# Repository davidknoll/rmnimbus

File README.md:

Projects and tools I've made while tinkering with the RM Nimbus PC-186 & PC-386
===============================================================================

Unless otherwise stated, anything here that was made by me can be used/distributed/etc under the MIT license, and none of it is approved or endorsed by [RM plc](https://www.rm.com/).

* ***8087repro*** - Reproduction of the 8087 option board for the PC-186, using a DS1100 delay line IC instead of EP8274. Prototype PCB passes basic testing.
* ***idecf*** - Ideas for how to attach a CF card to the PC-386, which uses the MCA bus so the right hardware can be harder to find.
* ***joysticksplitter*** - Allows two Atari/Commodore joysticks to be connected, as mentioned in sections 2.5.5 and 2.16.4 of the Service Manual. Two buttons are supported per joystick on pins 6 and 9, with power on pin 7. Not yet built/tested.
* ***nimbuscd*** - This contains some experiments with using a SCSI CD-ROM drive (initially, emulated with BlueSCSI) on the PC-186 with original DCB. I'm hoping to make it into `nimbuscd.sys`, a CD-ROM device driver to use with MSCDEX.
* ***nimbusmouse*** - I saw [this PS/2 mouse adaptor](https://www.thenimbus.co.uk/upgrades-and-maintenance/ps2mouse) and thought it could be done with a smaller microcontroller (specifically, an ATtiny2313 using [ATTinyCore](https://github.com/SpenceKonde/ATTinyCore)).
  * My version isn't working at the moment, but I've had aspects of it working. Work in progress.
* ***nimbusrtc*** - Attach a DS12C887A RTC pretty much directly to the bus as an expansion card.
  * This and similar RTCs are made for a multiplexed bus, so no extra latches and buffers are necessary. But because the Nimbus I/O bus is just half of a 16-bit bus, it only sees accesses where A0 is 0. The bus is shifted by one bit to make sure A0 can be 0 and the RTC registers can all still be accessed. The shift is reversed in software.
  * Not all of the RTC's RAM is accessible due to the available address space in one slot. Only chip selects 0, 2 and 4 can be used, as we also need to make sure A7 is 0 to address the right half of the RTC. Chip select 0 and interrupt 0 are generally reserved for the disk controller. An interrupt is unnecessary for the RTC if only using simple get/set commands.
  * There is a device driver that can be loaded from CONFIG.SYS to use the RTC on startup and with the TIME and DATE commands.
  * Alternatively, the get/set commands provided can be compiled on the Nimbus itself using Microsoft QuickC under SETPC. They default to expecting the RTC in slot 4, but this can be set with a switch ```/0``` - ```/4```.
* ***PC-386 RAM*** - Incomplete attempts at reproducing a decent size memory module for the PC-386.
* ***Piconet transceiver*** - Facilitates connecting a microcontroller to Piconet. Prototype PCBs so far untested- suspected pinout problem.
* ***piexpansion*** - Put a Raspberry Pi Pico W with an SD card on the PC-186 expansion bus, to hopefully emulate any physical expansion card, even the disk controller. Prototype PCB passes basic testing.
* ***reink*** - Generate block 0 for SCSI disks of any geometry, so you're not restricted to the few models in HDFORM.
  * This doesn't write the sector to the disk itself, as I don't have access to the system programmer's manual that would probably tell me how to do that. The sector is written to stdout instead, and you'll need to write it to the disk separately. (Which is made a whole lot simpler if using a SCSI2SD.)
  * You then need to run STAMP and/or HARDDISK on the Nimbus to partition the disk. I found a 64MB limit on DOS partition size, with only one DOS partition supported per disk.
  * This is not a replacement for an actual low-level format if you need one.
* ***simmadaptor*** - Adaptors for 30 or 72 pin SIMMs on the 186. Not yet tested, prototype PCBs ordered.
* ***ymplay*** - Play YM chiptune audio files using the AY-3-8910 in the Nimbus.

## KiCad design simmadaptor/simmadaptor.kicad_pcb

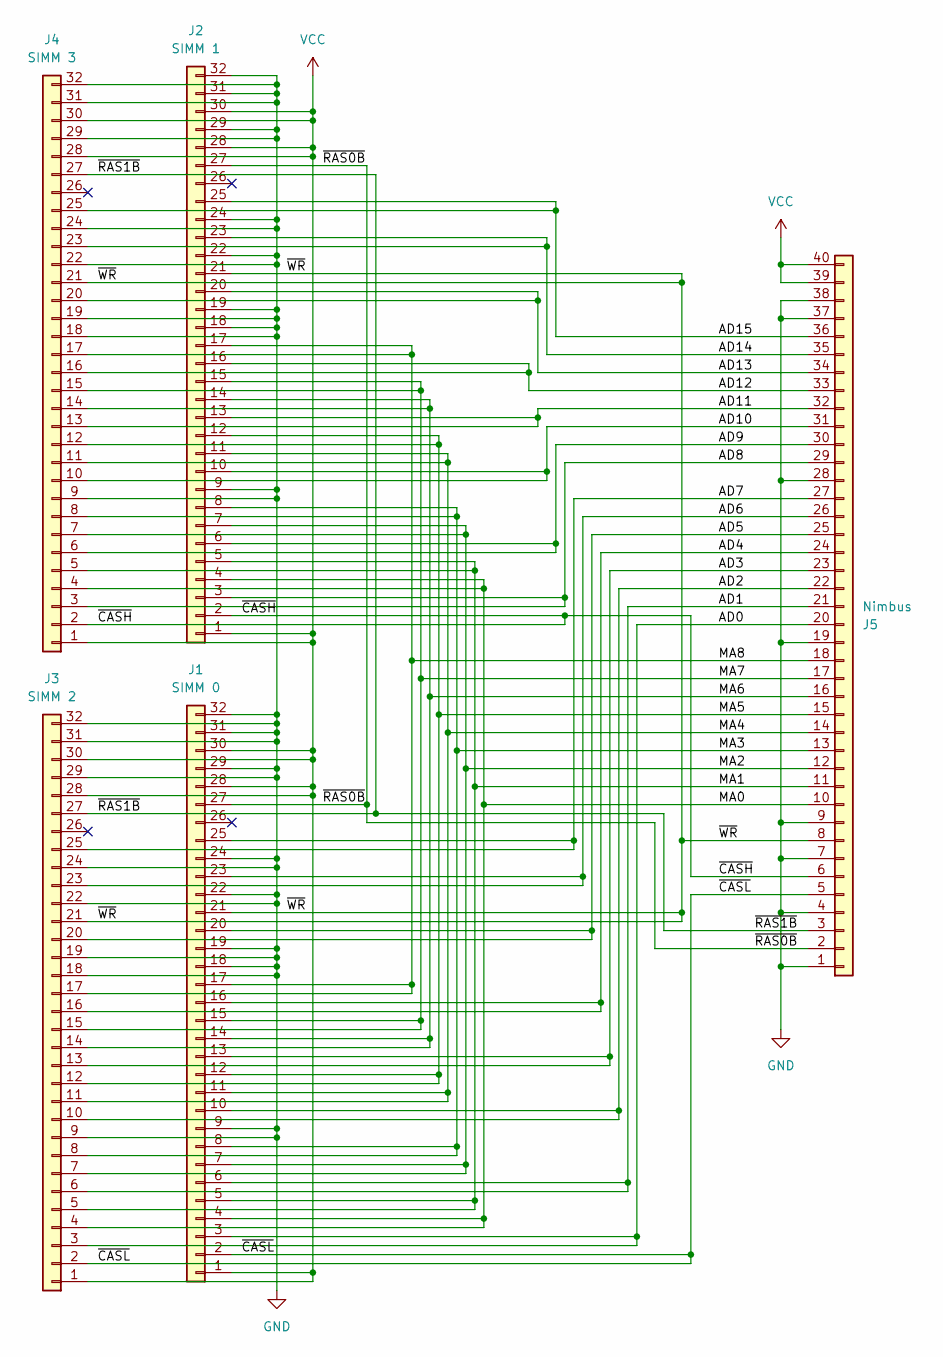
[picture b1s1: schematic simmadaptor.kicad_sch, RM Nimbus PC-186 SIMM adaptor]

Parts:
J1: SIMM 0; SIMM
J2: SIMM 1; SIMM
J3: SIMM 2; SIMM
J4: SIMM 3; SIMM
J5: Nimbus; PinSocket_1x40_P2.54mm_Horizontal

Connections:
/AD0: J1.3, J3.3, J5.20
/AD1: J1.6, J3.6, J5.21
/AD2: J1.10, J3.10, J5.22
/AD3: J1.13, J3.13, J5.23
/AD4: J1.16, J3.16, J5.24
/AD5: J1.20, J3.20, J5.25
/AD6: J1.23, J3.23, J5.26
/AD7: J1.25, J3.25, J5.27
/AD8: J2.3, J4.3, J5.29
/AD9: J2.6, J4.6, J5.30
/AD10: J2.10, J4.10, J5.31
/AD11: J2.13, J4.13, J5.32
/AD12: J2.16, J4.16, J5.33
/AD13: J2.20, J4.20, J5.34
/AD14: J2.23, J4.23, J5.35
/AD15: J2.25, J4.25, J5.36
/MA0: J1.4, J2.4, J3.4, J4.4, J5.10
/MA1: J1.5, J2.5, J3.5, J4.5, J5.11
/MA2: J1.7, J2.7, J3.7, J4.7, J5.12
/MA3: J1.8, J2.8, J3.8, J4.8, J5.13
/MA4: J1.11, J2.11, J3.11, J4.11, J5.14
/MA5: J1.12, J2.12, J3.12, J4.12, J5.15
/MA6: J1.14, J2.14, J3.14, J4.14, J5.16
/MA7: J1.15, J2.15, J3.15, J4.15, J5.17
/MA8: J1.17, J2.17, J3.17, J4.17, J5.18
/~CASH: J2.2, J4.2, J5.6
/~CASL: J1.2, J3.2, J5.5
/~RAS0B: J1.27, J2.27, J5.2
/~RAS1B: J3.27, J4.27, J5.3
/~WR: J1.21, J2.21, J3.21, J4.21, J5.8
GND: J1.9, J1.18, J1.19, J1.22, J1.24, J1.29, J1.31, J1.32, J2.9, J2.18, J2.19, J2.22, J2.24, J2.29, J2.31, J2.32, J3.9, J3.18, J3.19, J3.22, J3.24, J3.29, J3.31, J3.32, J4.9, J4.18, J4.19, J4.22, J4.24, J4.29, J4.31, J4.32, J5.1, J5.4, J5.7, J5.9, J5.19, J5.28, J5.37, J5.38
VCC: J1.1, J1.28, J1.30, J2.1, J2.28, J2.30, J3.1, J3.28, J3.30, J4.1, J4.28, J4.30, J5.39, J5.40

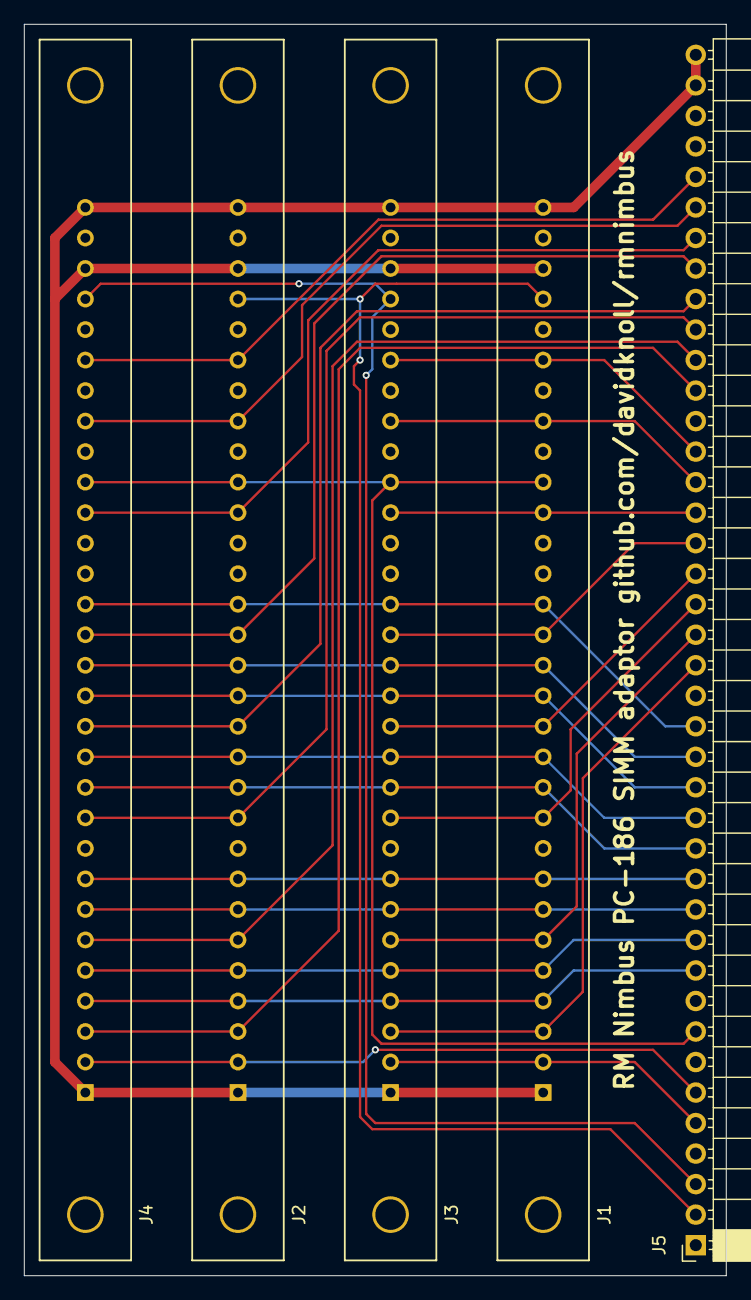
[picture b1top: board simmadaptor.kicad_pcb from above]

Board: 2 copper layers, 58.4 x 104.1 mm, 5 parts (0 on the bottom side), 32 nets.

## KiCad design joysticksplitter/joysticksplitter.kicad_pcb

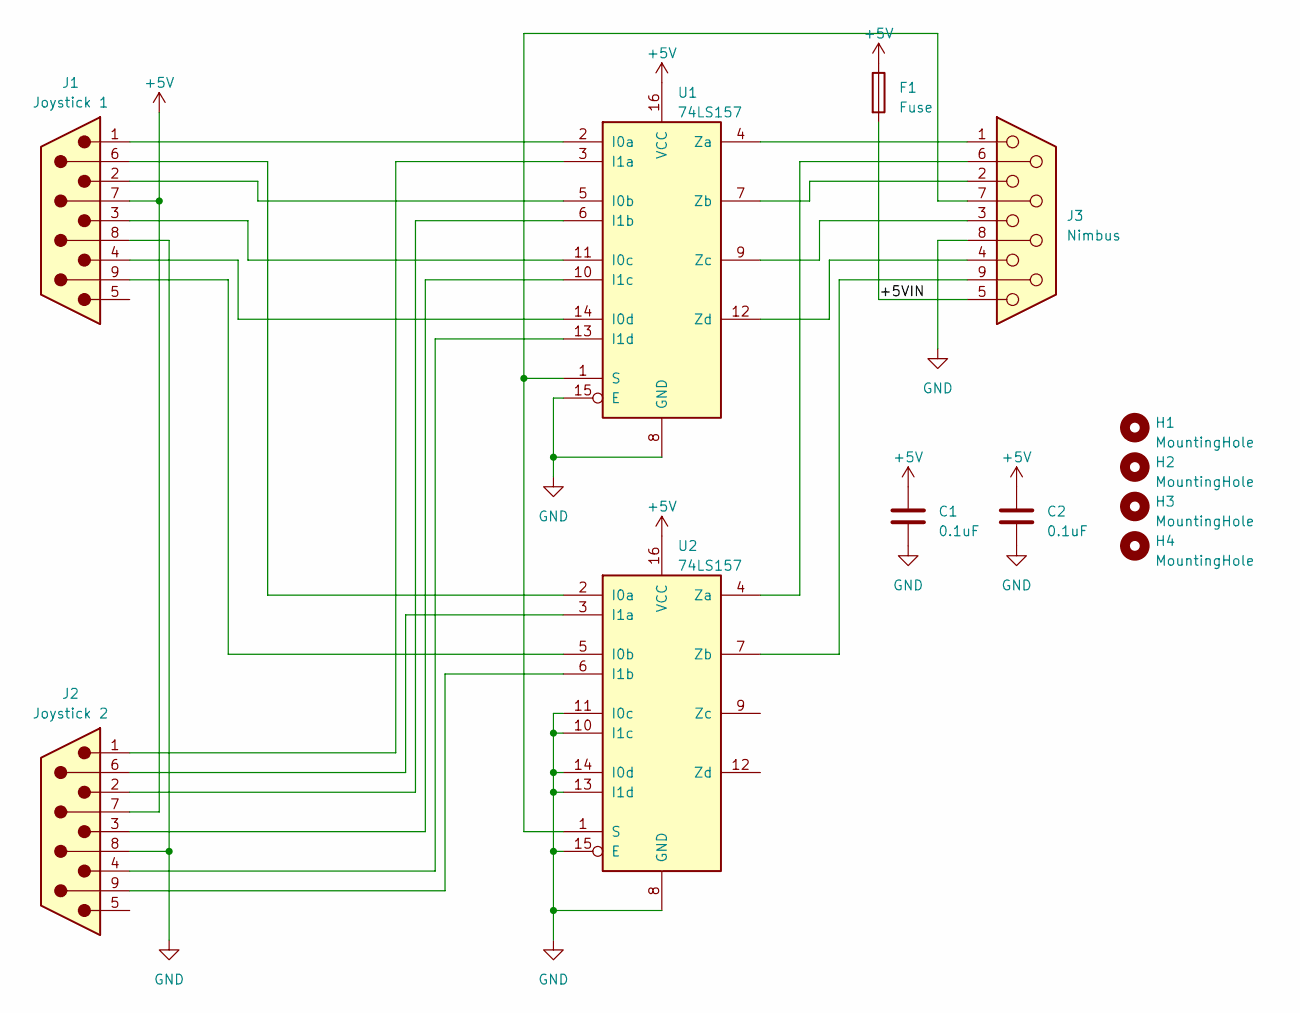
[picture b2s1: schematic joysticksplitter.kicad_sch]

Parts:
C1, C2: 0.1uF; C_Disc_D4.3mm_W1.9mm_P5.00mm
F1: Fuse; Fuse_Littelfuse_395Series
H1, H2, H3, H4: MountingHole; MountingHole_3.2mm_M3
J1: Joystick 1; DSUB-9_Male_EdgeMount_P2.77mm
J2: Joystick 2; DSUB-9_Male_EdgeMount_P2.77mm
J3: Nimbus; DSUB-9_Female_Horizontal_P2.77x2.84mm_EdgePinOffset9.40mm
U1, U2: 74LS157; DIP-16_W7.62mm_Socket

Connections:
+5V: C1.1, C2.1, F1.1, J1.7, J2.7, U1.16 (VCC), U2.16 (VCC)
/+5VIN: F1.2, J3.5
GND: C1.2, C2.2, J1.8, J2.8, J3.8, U1.8 (GND), U1.15 (E), U2.8 (GND), U2.10 (I1c), U2.11 (I0c), U2.13 (I1d), U2.14 (I0d), U2.15 (E)
unnamed: J1.1, U1.2 (I0a)
unnamed: J1.2, U1.5 (I0b)
unnamed: J1.3, U1.11 (I0c)
unnamed: J1.4, U1.14 (I0d)
unnamed: J2.1, U1.3 (I1a)
unnamed: J2.2, U1.6 (I1b)
unnamed: J2.3, U1.10 (I1c)
unnamed: J2.4, U1.13 (I1d)
unnamed: J3.7, U1.1 (S), U2.1 (S)
unnamed: J3.1, U1.4 (Za)
unnamed: J3.2, U1.7 (Zb)
unnamed: J3.3, U1.9 (Zc)
unnamed: J3.4, U1.12 (Zd)
unnamed: J1.6, U2.2 (I0a)
unnamed: J1.9, U2.5 (I0b)
unnamed: J2.6, U2.3 (I1a)
unnamed: J2.9, U2.6 (I1b)
unnamed: J3.6, U2.4 (Za)
unnamed: J3.9, U2.7 (Zb)

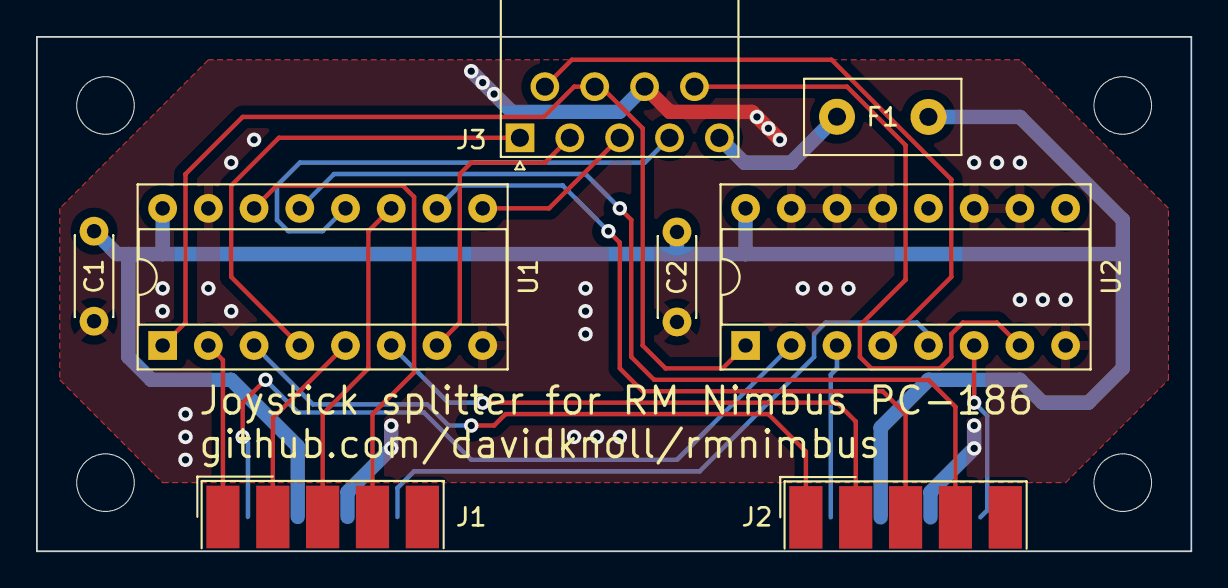
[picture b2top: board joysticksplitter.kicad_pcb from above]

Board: 2 copper layers, 64.1 x 28.6 mm, 12 parts (0 on the bottom side), 22 nets.

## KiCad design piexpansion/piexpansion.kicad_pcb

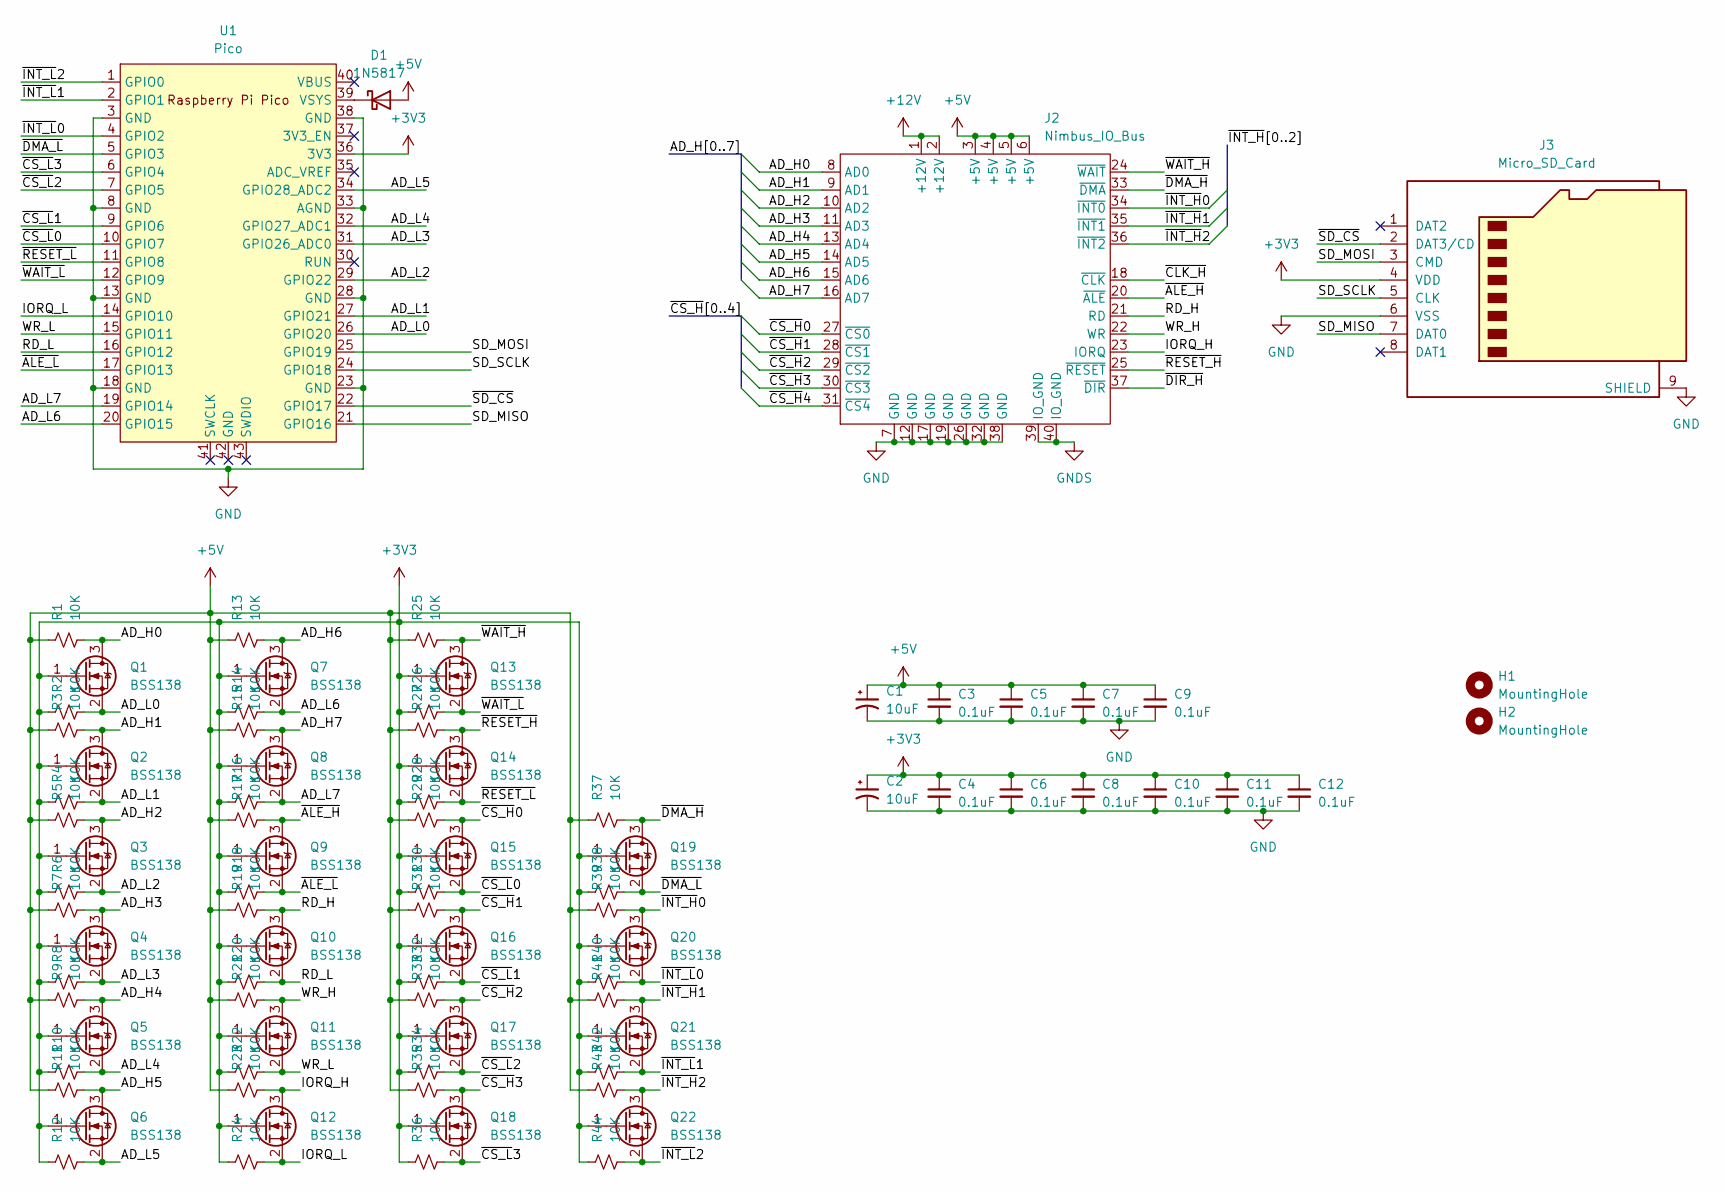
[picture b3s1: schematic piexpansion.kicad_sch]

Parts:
C1, C2: 10uF; CP_Radial_D6.3mm_P2.50mm
C3, C4, C5, C6, C7, C8, C9, C10, C11, C12: 0.1uF; C_0805_2012Metric_Pad1.18x1.45mm_HandSolder
D1: 1N5817; D_DO-41_SOD81_P10.16mm_Horizontal
H1, H2: MountingHole; MountingHole_4mm
J2: Nimbus_IO_Bus; IDC-Header_2x20-1MP_P2.54mm_Latch_Horizontal
J3: Micro_SD_Card; microSD_HC_Wuerth_693072010801
Q1, Q2, Q3, Q4, Q5, Q6, Q7, Q8, Q9, Q10, Q11, Q12, Q13, Q14, Q15, Q16, Q17, Q18, Q19, Q20, Q21, Q22: BSS138; SOT-23
R1, R2, R3, R4, R5, R6, R7, R8, R9, R10, R11, R12, R13, R14, R15, R16, R17, R18, R19, R20, R21, R22, R23, R24, R25, R26, R27, R28, R29, R30, R31, R32, R33, R34, R35, R36, R37, R38, R39, R40, R41, R42, R43, R44: 10K; R_0805_2012Metric_Pad1.20x1.40mm_HandSolder
U1: Pico; RPi_Pico_SMD_TH

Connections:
+3V3: C2.1, C4.1, C6.1, C8.1, C10.1, C11.1, C12.1, J3.4 (VDD), Q1.1 (G), Q2.1 (G), Q3.1 (G), Q4.1 (G), Q5.1 (G), Q6.1 (G), Q7.1 (G), Q8.1 (G), Q9.1 (G), Q10.1 (G), Q11.1 (G), Q12.1 (G), Q13.1 (G), Q14.1 (G), Q15.1 (G), Q16.1 (G), Q17.1 (G), Q18.1 (G), Q19.1 (G), Q20.1 (G), Q21.1 (G), Q22.1 (G), R2.1, R4.1, R6.1, R8.1, R10.1, R12.1, R14.1, R16.1, R18.1, R20.1, R22.1, R24.1, R26.1, R28.1, R30.1, R32.1, R34.1, R36.1, R38.1, R40.1, R42.1, R44.1, U1.36 (3V3)
+5V: C1.1, C3.1, C5.1, C7.1, C9.1, D1.2 (A), J2.3 (+5V), J2.4 (+5V), J2.5 (+5V), J2.6 (+5V), R1.1, R3.1, R5.1, R7.1, R9.1, R11.1, R13.1, R15.1, R17.1, R19.1, R21.1, R23.1, R25.1, R27.1, R29.1, R31.1, R33.1, R35.1, R37.1, R39.1, R41.1, R43.1
+12V: J2.1 (+12V), J2.2 (+12V)
/AD_H0: J2.8 (AD0), Q1.3 (D), R1.2
/AD_H1: J2.9 (AD1), Q2.3 (D), R3.2
/AD_H2: J2.10 (AD2), Q3.3 (D), R5.2
/AD_H3: J2.11 (AD3), Q4.3 (D), R7.2
/AD_H4: J2.13 (AD4), Q5.3 (D), R9.2
/AD_H5: J2.14 (AD5), Q6.3 (D), R11.2
/AD_H6: J2.15 (AD6), Q7.3 (D), R13.2
/AD_H7: J2.16 (AD7), Q8.3 (D), R15.2
/AD_L0: Q1.2 (S), R2.2, U1.26 (GPIO20)
/AD_L1: Q2.2 (S), R4.2, U1.27 (GPIO21)
/AD_L2: Q3.2 (S), R6.2, U1.29 (GPIO22)
/AD_L3: Q4.2 (S), R8.2, U1.31 (GPIO26_ADC0)
/AD_L4: Q5.2 (S), R10.2, U1.32 (GPIO27_ADC1)
/AD_L5: Q6.2 (S), R12.2, U1.34 (GPIO28_ADC2)
/AD_L6: Q7.2 (S), R14.2, U1.20 (GPIO15)
/AD_L7: Q8.2 (S), R16.2, U1.19 (GPIO14)
/IORQ_H: J2.23 (IORQ), Q12.3 (D), R23.2
/IORQ_L: Q12.2 (S), R24.2, U1.14 (GPIO10)
/RD_H: J2.21 (RD), Q10.3 (D), R19.2
/RD_L: Q10.2 (S), R20.2, U1.16 (GPIO12)
/SD_MISO: J3.7 (DAT0), U1.21 (GPIO16)
/SD_MOSI: J3.3 (CMD), U1.25 (GPIO19)
/SD_SCLK: J3.5 (CLK), U1.24 (GPIO18)
/WR_H: J2.22 (WR), Q11.3 (D), R21.2
/WR_L: Q11.2 (S), R22.2, U1.15 (GPIO11)
/~ALE_H: J2.20 (~ALE), Q9.3 (D), R17.2
/~ALE_L: Q9.2 (S), R18.2, U1.17 (GPIO13)
/~CLK_H: J2.18 (~CLK)
/~CS_H0: J2.27 (~CS0), Q15.3 (D), R29.2
/~CS_H1: J2.28 (~CS1), Q16.3 (D), R31.2
/~CS_H2: J2.29 (~CS2), Q17.3 (D), R33.2
/~CS_H3: J2.30 (~CS3), Q18.3 (D), R35.2
/~CS_H4: J2.31 (~CS4)
/~CS_L0: Q15.2 (S), R30.2, U1.10 (GPIO7)
/~CS_L1: Q16.2 (S), R32.2, U1.9 (GPIO6)
/~CS_L2: Q17.2 (S), R34.2, U1.7 (GPIO5)
/~CS_L3: Q18.2 (S), R36.2, U1.6 (GPIO4)
/~DIR_H: J2.37 (~DIR)
/~DMA_H: J2.33 (~DMA), Q19.3 (D), R37.2
/~DMA_L: Q19.2 (S), R38.2, U1.5 (GPIO3)
/~INT_H0: J2.34 (~INT0), Q20.3 (D), R39.2
/~INT_H1: J2.35 (~INT1), Q21.3 (D), R41.2
/~INT_H2: J2.36 (~INT2), Q22.3 (D), R43.2
/~INT_L0: Q20.2 (S), R40.2, U1.4 (GPIO2)
/~INT_L1: Q21.2 (S), R42.2, U1.2 (GPIO1)
/~INT_L2: Q22.2 (S), R44.2, U1.1 (GPIO0)
/~RESET_H: J2.25 (~RESET), Q14.3 (D), R27.2
/~RESET_L: Q14.2 (S), R28.2, U1.11 (GPIO8)
/~SD_CS: J3.2 (DAT3/CD), U1.22 (GPIO17)
/~WAIT_H: J2.24 (~WAIT), Q13.3 (D), R25.2
/~WAIT_L: Q13.2 (S), R26.2, U1.12 (GPIO9)
GND: C1.2, C2.2, C3.2, C4.2, C5.2, C6.2, C7.2, C8.2, C9.2, C10.2, C11.2, C12.2, J2.7 (GND), J2.12 (GND), J2.17 (GND), J2.19 (GND), J2.26 (GND), J2.32 (GND), J2.38 (GND), J3.6 (VSS), J3.9 (SHIELD), U1.3 (GND), U1.8 (GND), U1.13 (GND), U1.18 (GND), U1.23 (GND), U1.28 (GND), U1.33 (AGND), U1.38 (GND)
GNDS: J2.39 (IO_GND), J2.40 (IO_GND)
unnamed: D1.1 (K), U1.39 (VSYS)

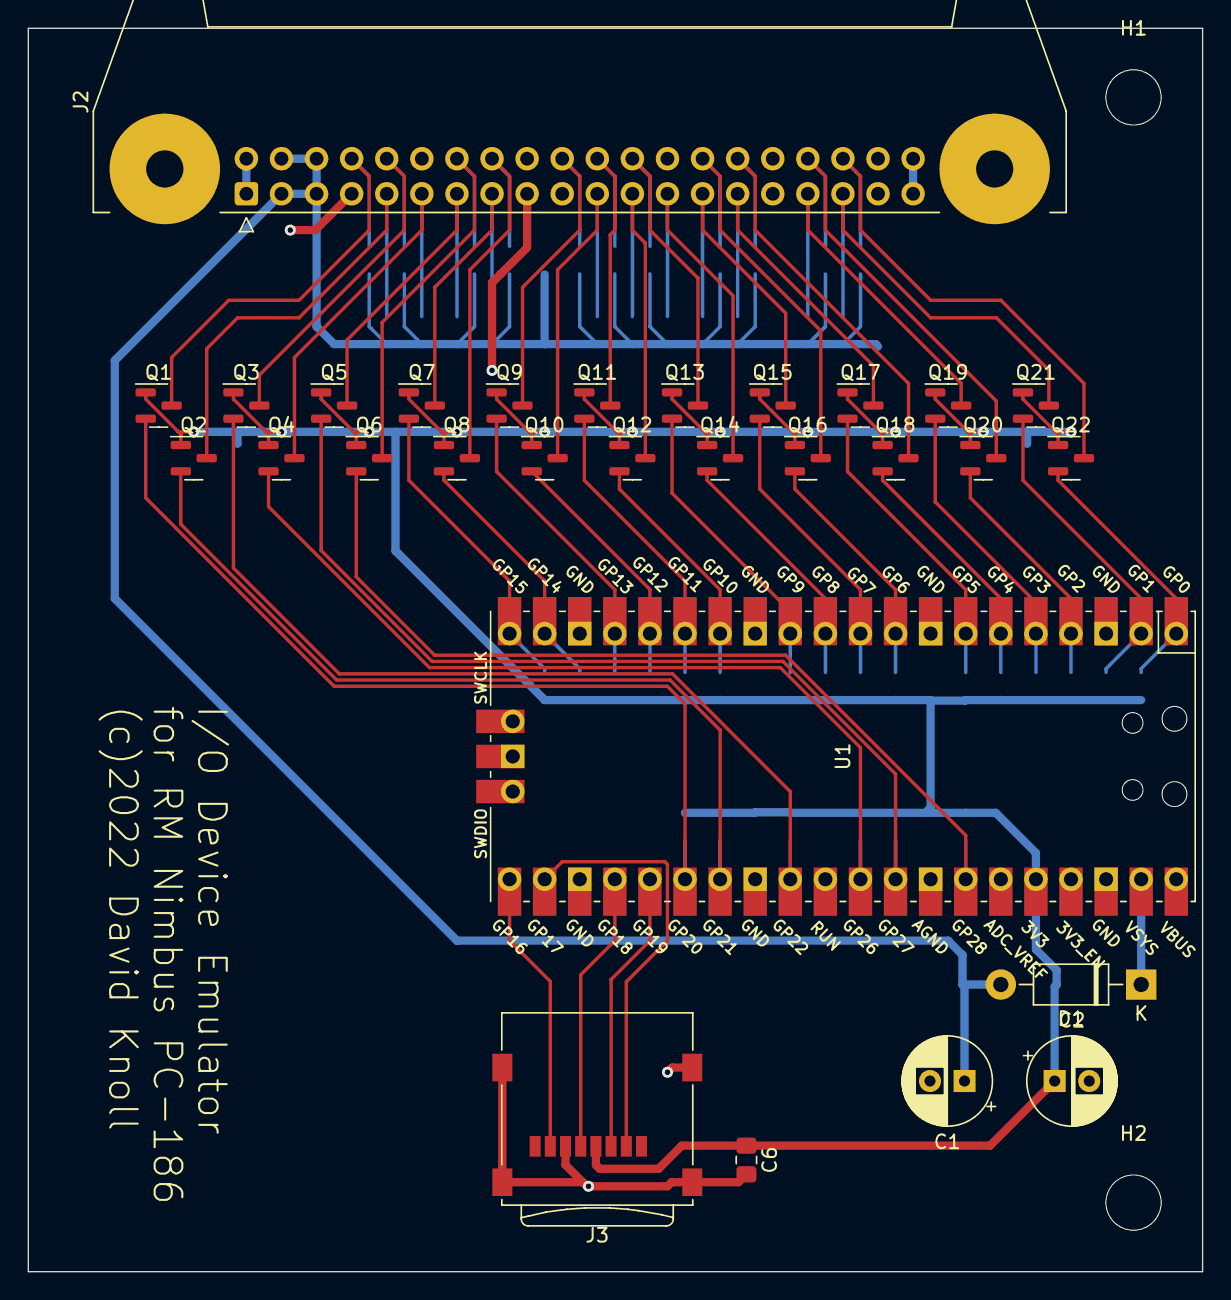
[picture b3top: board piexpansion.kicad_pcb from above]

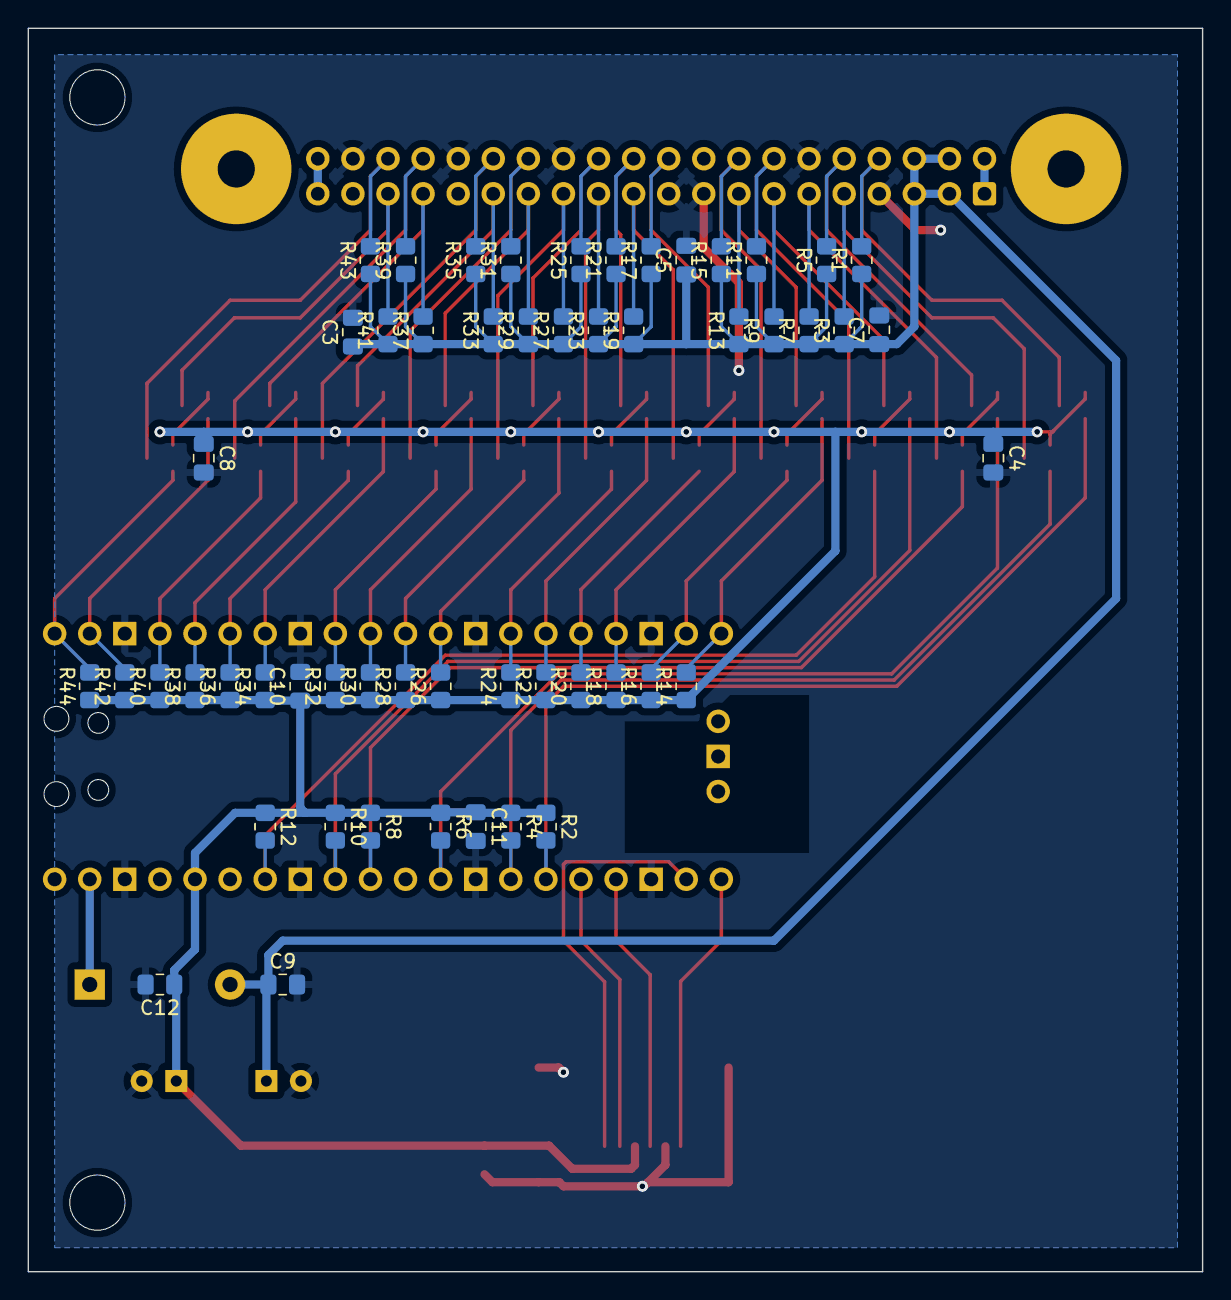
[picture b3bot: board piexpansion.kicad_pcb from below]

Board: 2 copper layers, 85.0 x 90.0 mm, 84 parts (53 on the bottom side), 54 nets.

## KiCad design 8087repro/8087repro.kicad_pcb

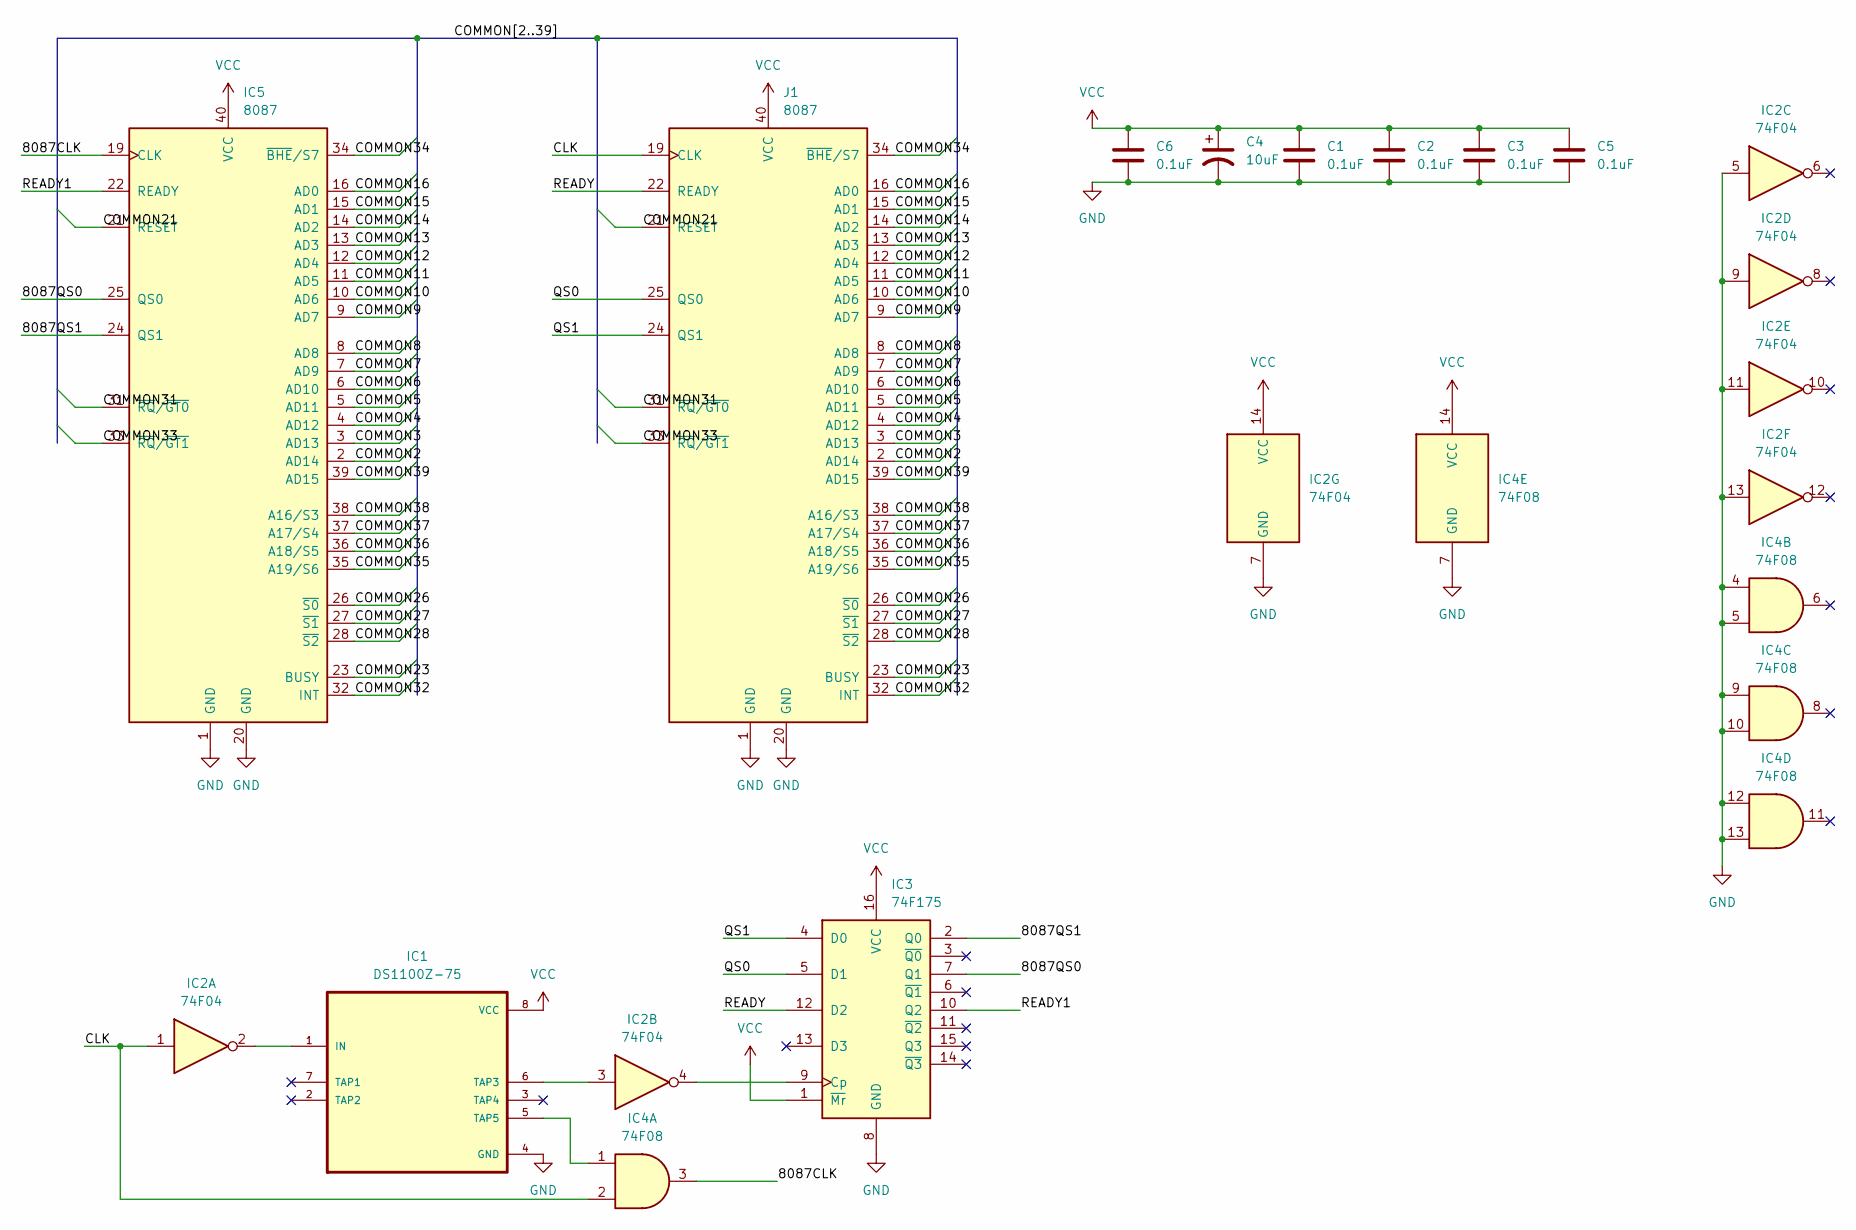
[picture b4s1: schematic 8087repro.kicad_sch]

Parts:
C1, C2, C3, C5, C6: 0.1uF; C_Disc_D5.0mm_W2.5mm_P5.00mm
C4: 10uF; C_Radial_D6.3mm_H5.0mm_P2.50mm
IC1: DS1100Z-75; SOIC127P600X175-8N
IC2: 74F04; DIP-14_W7.62mm_Socket_LongPads
IC3: 74F175; DIP-16_W7.62mm_Socket_LongPads
IC4: 74F08; DIP-14_W7.62mm_Socket_LongPads
IC5: 8087; DIP-40_W15.24mm
J1: 8087; DIP-40_W15.24mm

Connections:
/8087CLK: IC4.3, IC5.19 (CLK)
/8087QS0: IC3.7 (Q1), IC5.25 (QS0)
/8087QS1: IC3.2 (Q0), IC5.24 (QS1)
/CLK: IC2.1, IC4.2, J1.19 (CLK)
/COMMON2: IC5.2 (AD14), J1.2 (AD14)
/COMMON3: IC5.3 (AD13), J1.3 (AD13)
/COMMON4: IC5.4 (AD12), J1.4 (AD12)
/COMMON5: IC5.5 (AD11), J1.5 (AD11)
/COMMON6: IC5.6 (AD10), J1.6 (AD10)
/COMMON7: IC5.7 (AD9), J1.7 (AD9)
/COMMON8: IC5.8 (AD8), J1.8 (AD8)
/COMMON9: IC5.9 (AD7), J1.9 (AD7)
/COMMON10: IC5.10 (AD6), J1.10 (AD6)
/COMMON11: IC5.11 (AD5), J1.11 (AD5)
/COMMON12: IC5.12 (AD4), J1.12 (AD4)
/COMMON13: IC5.13 (AD3), J1.13 (AD3)
/COMMON14: IC5.14 (AD2), J1.14 (AD2)
/COMMON15: IC5.15 (AD1), J1.15 (AD1)
/COMMON16: IC5.16 (AD0), J1.16 (AD0)
/COMMON21: IC5.21 (RESET), J1.21 (RESET)
/COMMON23: IC5.23 (BUSY), J1.23 (BUSY)
/COMMON26: IC5.26 (~S0), J1.26 (~S0)
/COMMON27: IC5.27 (~S1), J1.27 (~S1)
/COMMON28: IC5.28 (~S2), J1.28 (~S2)
/COMMON31: IC5.31 (~RQ/~GT0), J1.31 (~RQ/~GT0)
/COMMON32: IC5.32 (INT), J1.32 (INT)
/COMMON33: IC5.33 (~RQ/~GT1), J1.33 (~RQ/~GT1)
/COMMON34: IC5.34 (~BHE/S7), J1.34 (~BHE/S7)
/COMMON35: IC5.35 (A19/S6), J1.35 (A19/S6)
/COMMON36: IC5.36 (A18/S5), J1.36 (A18/S5)
/COMMON37: IC5.37 (A17/S4), J1.37 (A17/S4)
/COMMON38: IC5.38 (A16/S3), J1.38 (A16/S3)
/COMMON39: IC5.39 (AD15), J1.39 (AD15)
/QS0: IC3.5 (D1), J1.25 (QS0)
/QS1: IC3.4 (D0), J1.24 (QS1)
/READY: IC3.12 (D2), J1.22 (READY)
/READY1: IC3.10 (Q2), IC5.22 (READY)
GND: C1.2, C2.2, C3.2, C4.2, C5.2, C6.2, IC1.4 (GND), IC2.5, IC2.7 (GND), IC2.9, IC2.11, IC2.13, IC3.8 (GND), IC4.4, IC4.5, IC4.7 (GND), IC4.9, IC4.10, IC4.12, IC4.13, IC5.1 (GND), IC5.20 (GND), J1.1 (GND), J1.20 (GND)
unnamed: IC1.1 (IN), IC2.2
unnamed: IC1.5 (TAP5), IC4.1
unnamed: IC1.6 (TAP3), IC2.3
unnamed: IC2.4, IC3.9 (Cp)
VCC: C1.1, C2.1, C3.1, C4.1, C5.1, C6.1, IC1.8 (VCC), IC2.14 (VCC), IC3.1 (~Mr), IC3.16 (VCC), IC4.14 (VCC), IC5.40 (VCC), J1.40 (VCC)

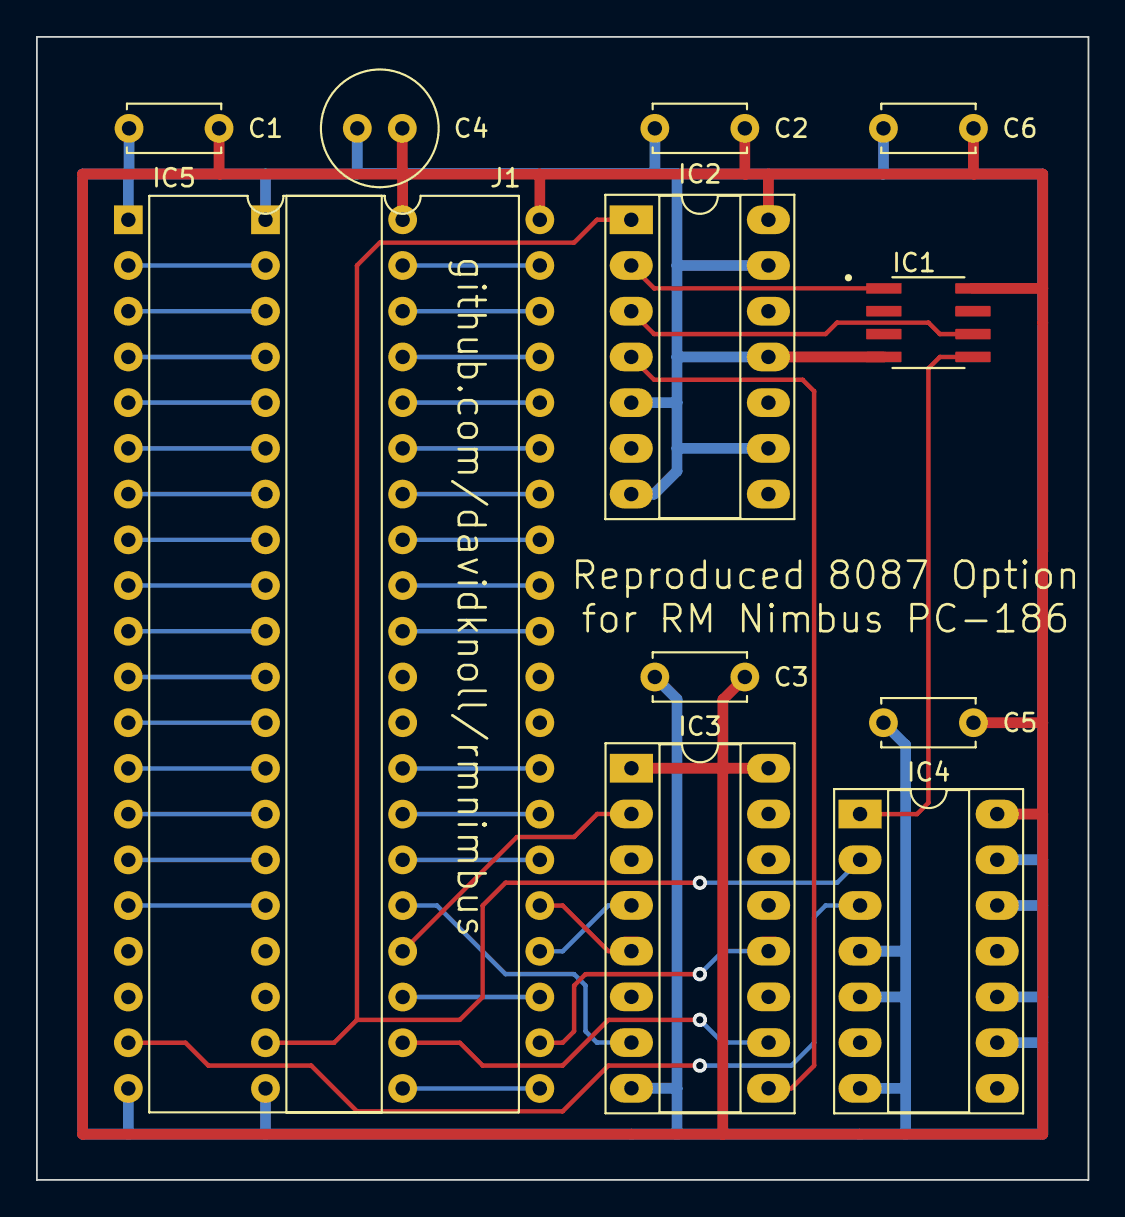
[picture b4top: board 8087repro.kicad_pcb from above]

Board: 2 copper layers, 58.4 x 63.5 mm, 12 parts (0 on the bottom side), 43 nets.

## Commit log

2021-09-09 Add stuff
2021-09-13 Add support for different slots and modes
2022-08-18 A whole bunch
2022-09-04 Test for some key parts of the I/O board
2022-09-08 test receiving data from the bus
2022-09-10 Working emulation of my RTC board, auto set over WiFi
2022-09-22 reorganisation
2022-09-23 Test IRQs on device emulator
2022-10-21 Attempt at emulating parallel printer card, not working probably due to something with interrupts / acknowledge signal
2022-10-26 Emulate the DCC card
    Seems to work for Kermit, including the rx interrupt, but fails DCCPT
    badly because I don't emulate the test jig. Also doesn't emulate DMA.
2022-10-31 DCC: DMA (not tested), improve debug messages
2022-11-01 Multiple devices coexisting
2023-02-13 Experiment with accessing a SCSI CD-ROM
2023-02-15 nimbuscd: add inquiry test, add timeouts
2023-02-24 first test version of cd driver, mscdex freezes
2023-02-25 A command to probe devices on the Nimbus SASI bus
2023-02-25 preliminary untested fdc emulation, left disabled
2023-03-28 Design a joystick splitter
2023-03-28 Add skeleton CD write function, emulate DCC B for future use
2024-11-28 Add CLOCK$ device driver for Dallas RTC
2024-12-04 Fix bug in RTC driver when card not present, more features for the Pico RTC emulation, Bluetooth debug channel
2025-01-11 wip sasi emulation bits that also arent tested
2025-01-13 begin to c++ify the card slots, add periodic interrupt support to rtc
2025-01-13 c++ify the parallel device
2025-01-14 c++ify the dcc device
2025-01-14 reset and device slots stuff
2025-01-14 rename some files
2025-02-10 SIMM adaptors for the 186
2025-03-11 YM audio player
2025-03-11 Tolerate but don't implement YM6, digidrums, and additional data
2025-03-12 Minor corrections
2025-03-15 Support more formats
2025-03-15 indicate compressed files
2025-05-17 Reorganise some stuff, add the multi device and its driver
    Although the RTC examples seem to work, there is some spurious/incorrect data when emulating a character device- possibly PIO, possibly hardware/logic level?

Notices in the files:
piexpansion/piexpansion.kicad_pcb:
(c)2022 David Knoll
